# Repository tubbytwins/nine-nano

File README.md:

# Nine keyboard

The Nine keyboard and its variants open up new possibilities for split wireless keyboard applications, as well as one-handed keyboard/keypad applications that rely on reduced-key layouts and take advantage of chording, layers, and other clever firmware features to provide novel typing experiences with reduced finger motion.

The [variants page](docs/variants_5o16_5o17.md) provides more detail on the added-key variants.

(Remaining text below was written by the original author "ButShesAGirl")

The Nine is a tiny 18-key split, wireless, ergonomic split keyboard, heavily inspired by Ben Vallack's [Piano 2](https://www.pcbway.com/project/shareproject/The_Piano_by_Ben_Vallack_Ultra_minimal_18_key_keyboard_5b2c99e1.html). I tried out his design and loved it, but wanted to [tweak the physical layout](https://www.rousette.org.uk/archives/introducing-the-nine-keyboard/) a bit to fit my hands and my use case better. It uses Nice!Nano V2 BLE-equipped controllers, and (optionally) Nice!View displays to show information like the connected BLE profile, battery level and layer name. You can read more about this keyboard and the design decisions I made here: [Introducing the Nine keyboard](https://www.rousette.org.uk/archives/introducing-the-nine-keyboard/) and [Nine keyboard Part 2 - the case](https://www.rousette.org.uk/archives/nine-keyboard-part-2-the-case/).

The PCB was generously sponsored by [PCBWay](https://www.pcbway.com/), who paid for the boards. I also got the case printed at PCBWay but paid for that myself. They did a fantastic, high quality job with both and I can highly recommend them. I would like to thank them for their sponsorship and support.

Note that while I provide the `.stl` files for a case which fits the PCB here and works well, I will probably tweak the case (and possibly the PCB design) a bit in future to provide better protection for the displays and controllers, and also possibly provide more options for case designs. If/when I do that, I will add a 'v2' of the case and PCB if necessary here. I may also create a version using the Seeed XIAO BLE controller, which is smaller physically and also slightly cheaper to buy (which is why I have called this repo 'nine-nano'!) In the meantime, I have provided all the necessary source KiCad files and the [Shapr3D](https://www.shapr3d.com/) source files if you want to adapt either design.

## PCB

All the PCB files are [here](pcb/). If you want to fabricate and build the keyboard, the easiest route is to upload the [zip file containing the Gerbers](pcb/nine-nano-gerbers.zip) to a PCB fabrication house like [PCBWay](https://www.pcbway.com/). I have written a [build guide](docs/build_guide.md) which should help you when soldering and assembling the board.

If you need information about how the board is wired up, PDFs of the [schematic](docs/nine_nano_schematic.pdf) and [PCB](docs/nine_nano_pcb.pdf) are provided, or you can open the [project](pcb/nine-nano.kicad_pro) in KiCad to alter the design yourself.

## Case

The `.stl` files needed to build the case, as well as the [Shapr3D source file](case/nine%20case.shapr) are in the [case](case/) directory. You will also find a file there with a basic 3D model of the PCB plus the main board components if you need a reference to build your own case. It's pretty bad though, as I couldn't figure out how to export the model with the surface-mounted components included. If you know how to improve this, please let me know --- it would have made designing the case much easier!

The [build guide](docs/build_guide.md) includes a section on getting the case printed and assembled too. Note that I have only got the case printed in resin, so I cannot guarantee that the tolerances etc. would be correct for printing in PLA or other materials. 

## Firmware

The [ZMK firmware](https://github.com/bsag/zmk-config-nine/) for this keyboard is in a separate repository, which you can fork if you would like to alter the keymapping. Instructions for downloading the firmware are in the [build guide](docs/build_guide.md). 

## Build guide

The build guide for the PCB and case can be found [here](docs/build_guide.md).

## Credits

As previously mentioned, this design is heavily inspired by Ben Vallack's [Piano 2](https://www.pcbway.com/project/shareproject/The_Piano_by_Ben_Vallack_Ultra_minimal_18_key_keyboard_5b2c99e1.html) and the layout he designed. I also used items from various repositories on Github for symbols and footprints to use in KiCad, such as [perigoso's keyswitch library](https://github.com/perigoso/keyswitch-kicad-library), [footstan's kbd library](https://github.com/foostan/kbd), and [crides kleeb library](https://github.com/crides/kleeb). 

Many thanks to the team at PCBWay for their help and support, particularly Liam.

The case design is my own, but I was hugely inspired by [Geist's TOTEM keyboard and case](https://github.com/GEIGEIGEIST/TOTEM), and his excellent build guide. Until seeing his case, I had no idea that you could print in transparent resin, which influenced a lot of my design decisions. He also has a beautiful build guide, which my poor illustration skills cannot hope to live up to!

Last but not least, I have asked a lot of questions and had invaluable advice from many people on the ZMK and Nice Keyboards Discords, including @petejohanson and @TweetyDaBird among others --- thanks for all who gave their time to help me, or who have open sourced their PCB designs, as this was really useful to check my work as I progressed with the designs ♥️. 

## Licence

This work is licenced with an [MIT license](LICENSE).

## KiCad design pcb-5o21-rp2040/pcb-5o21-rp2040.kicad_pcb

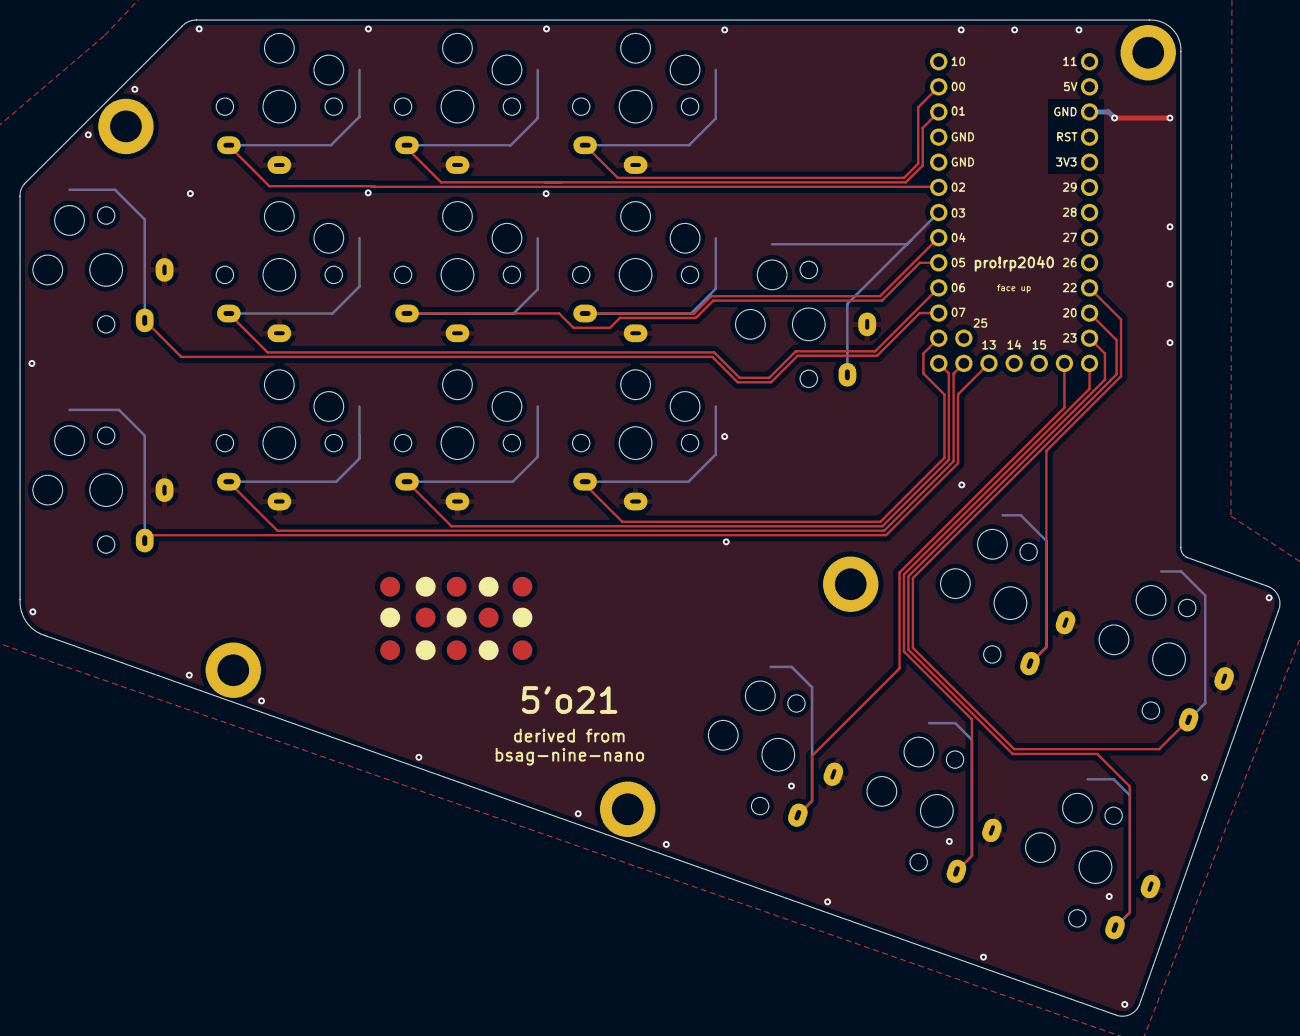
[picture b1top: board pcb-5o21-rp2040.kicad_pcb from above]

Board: 2 copper layers, 127.3 x 100.7 mm, 18 parts (0 on the bottom side), 18 nets.

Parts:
SW1, SW2, SW3, SW4, SW5, SW6, SW7, SW9, SW10, SW11, SW15, SW15#2: SW_Push; Kailh_PG1350_bw_1u_both
SW8, SW12, SW13, SW13#2, SW17: SW_Push; Kailh_PG1350_bw_1.5u_both
U1: nice_nano; rp2040_pro_micro_2x13

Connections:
D4: SW7.1, U1.7 (P0.22)
D5: SW6.1, U1.8 (P0.24)
D6: SW5.1, U1.9 (P1.00)
D7: SW1.1, U1.10 (P0.11)
D8: SW11.1, U1.11 (P1.04)
D9: SW10.1, U1.12 (P1.06)
D10: SW9.1, U1.14 (NFC2/P0.10)
D11: SW8.1, U1.15 (P1.11)
D12: SW17.1, U1.6 (P0.20)
D14: SW13.1, U1.19 (AIN5/P0.29)
D15: SW12.1, U1.18 (AIN0/P0.02)
D16: SW13#2.1, U1.20 (AIN7/P0.31)
D17: SW15.1, U1.21 (VCC)
D18: SW15#2.1, U1.22 (RST)
D19: SW2.1, U1.5 (P0.17)
D20: SW3.1, U1.2 (RX1/P0.08)
D21: SW4.1, U1.1 (TX0/P0.06)
GND: SW1.2, SW2.2, SW3.2, SW4.2, SW5.2, SW6.2, SW7.2, SW8.2, SW9.2, SW10.2, SW11.2, SW12.2, SW13.2, SW13#2.2, SW15.2, SW15#2.2, SW17.2, U1.29

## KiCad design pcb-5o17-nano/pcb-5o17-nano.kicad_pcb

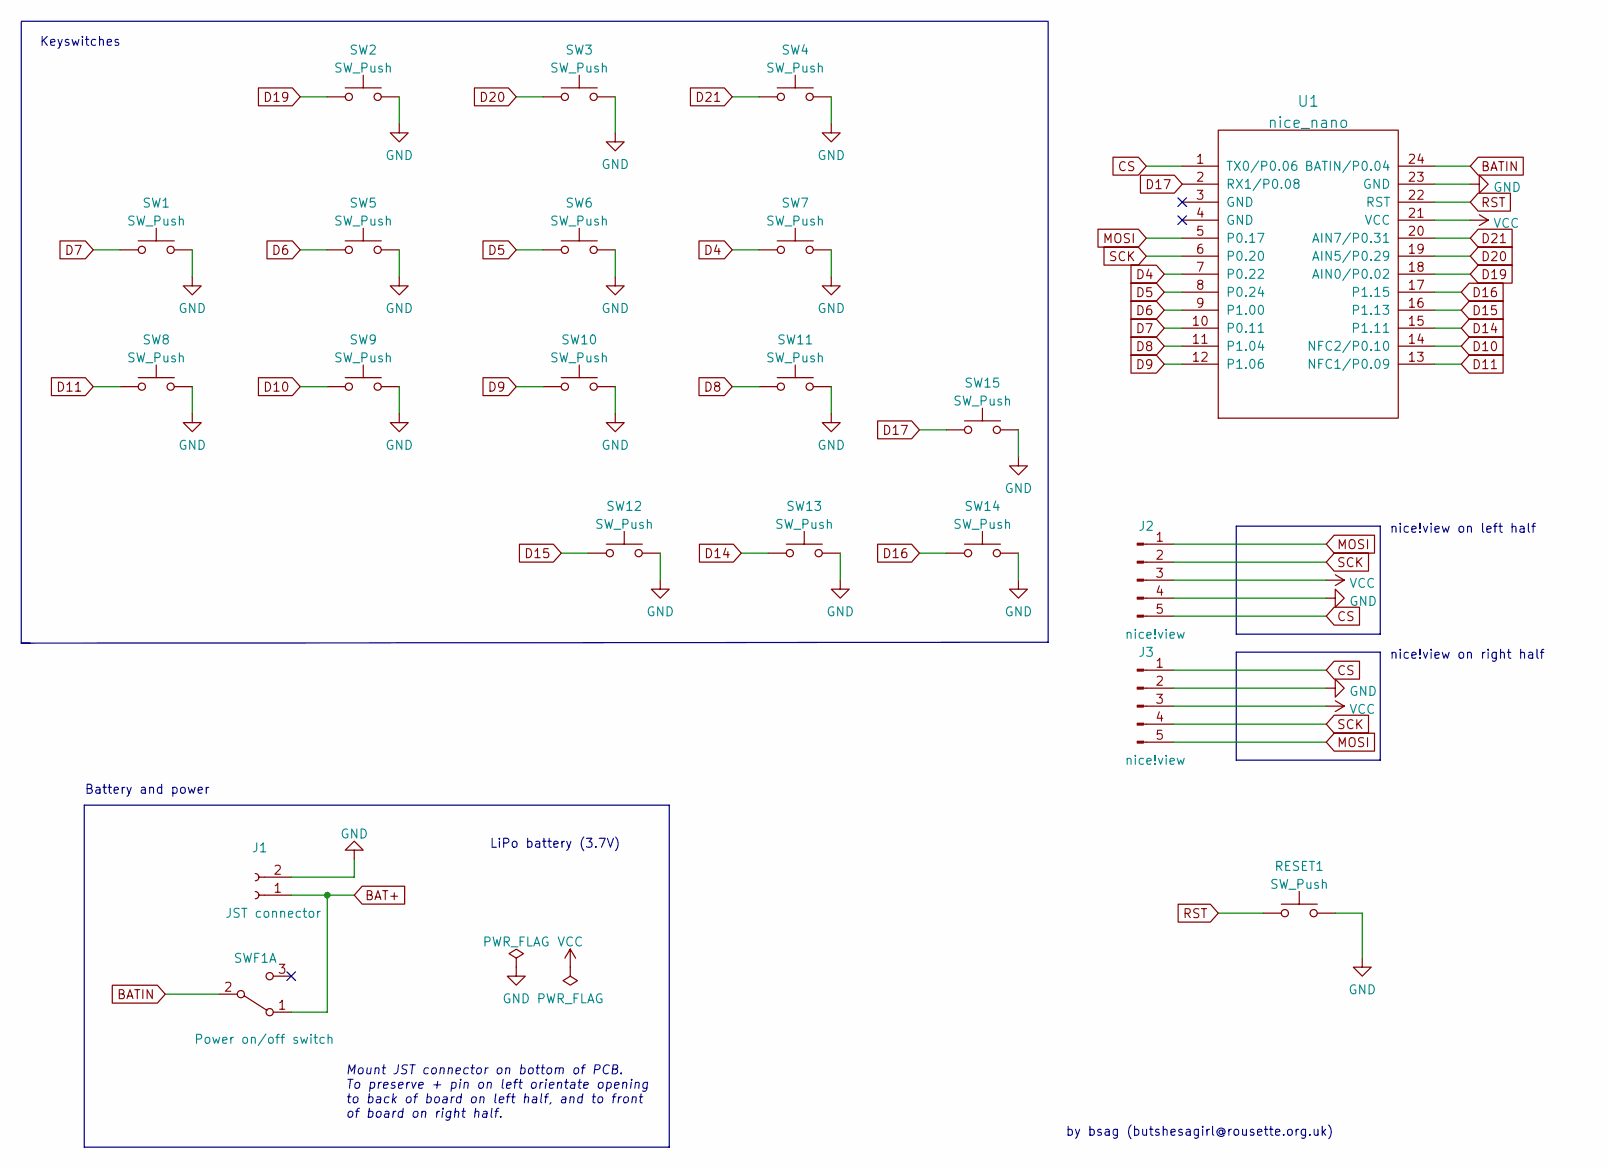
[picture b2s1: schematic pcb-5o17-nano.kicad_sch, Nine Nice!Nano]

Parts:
J1: JST connector; JST-ZH-2p-1.5
J2, J3: nice!view; OLED_5Pin
RESET1: SW_Push; b3u1000p
SW1, SW8, SW12, SW13, SW14, SW15: SW_Push; pg1350-rev-hs-1.25U
SW2, SW3, SW4, SW5, SW6, SW7, SW9, SW10, SW11: SW_Push; pg1350-rev-hs-1U
SWF1: Power on/off switch; pwr-sw-smd-pcm12
U1: nice_nano; nice-nano-no-rev

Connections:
BAT+: J1.1, SWF1.1 (A)
BATIN: SWF1.2 (B), U1.24 (BATIN/P0.04)
CS: J2.5, J3.1, U1.1 (TX0/P0.06)
D4: SW7.1, U1.7 (P0.22)
D5: SW6.1, U1.8 (P0.24)
D6: SW5.1, U1.9 (P1.00)
D7: SW1.1, U1.10 (P0.11)
D8: SW11.1, U1.11 (P1.04)
D9: SW10.1, U1.12 (P1.06)
D10: SW9.1, U1.14 (NFC2/P0.10)
D11: SW8.1, U1.13 (NFC1/P0.09)
D14: SW13.1, U1.15 (P1.11)
D15: SW12.1, U1.16 (P1.13)
D16: SW14.1, U1.17 (P1.15); also elsewhere on the board
D17: SW15.1, U1.2 (RX1/P0.08)
D19: SW2.1, U1.18 (AIN0/P0.02)
D20: SW3.1, U1.19 (AIN5/P0.29)
D21: SW4.1, U1.20 (AIN7/P0.31)
GND: J1.2, J2.4, J3.2, RESET1.2, SW1.2, SW2.2, SW3.2, SW4.2, SW5.2, SW6.2, SW7.2, SW8.2, SW9.2, SW10.2, SW11.2, SW12.2, SW13.2, SW15.2, U1.23 (GND); also elsewhere on the board
MOSI: J2.1, J3.5, U1.5 (P0.17)
RST: RESET1.1, U1.22 (RST)
SCK: J2.2, J3.4, U1.6 (P0.20)
VCC: J2.3, J3.3, U1.21 (VCC)

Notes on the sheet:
by bsag (butshesagirl@rousette.org.uk)
LiPo battery (3.7V)
Mount JST connector on bottom of PCB. To preserve + pin on left orientate opening to back of board on left half, and to front of board on right half.
nice!view on right half
Keyswitches
nice!view on left half
Battery and power

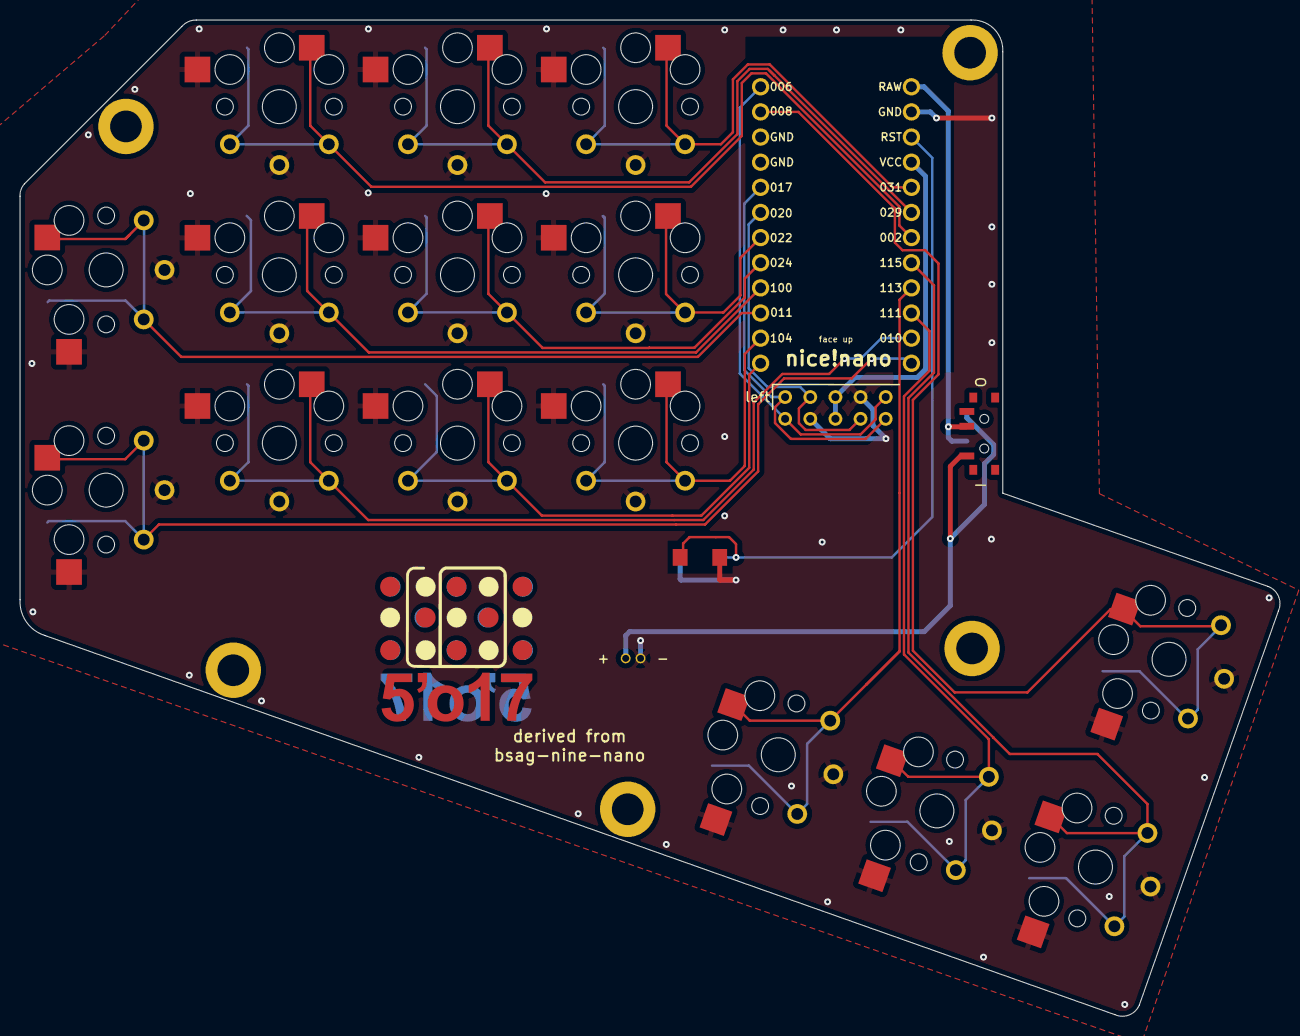
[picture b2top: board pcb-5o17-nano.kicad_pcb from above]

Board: 2 copper layers, 127.3 x 100.7 mm, 21 parts (0 on the bottom side), 23 nets.

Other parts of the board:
SW13#2: SW_Push; pg1350-rev-hs-1.25U

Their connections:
D16: SW13#2.1; also elsewhere on the board
GND: SW13#2.2; also elsewhere on the board

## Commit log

2023-08-26 New variants of nine-nano with either 5 or 6 added keys. This should give a bit more flexibility for those who might struggle with using reduced-key layouts (such as Ardux or Taipo).
2023-08-26 Added initial documentation for variants.
2023-08-26 Fixing a small typo.
2023-10-18 New 20-key and 21-key extended variants that work with an Elite-Pi, Elite-C, or RP2040 pro-micro clone.
